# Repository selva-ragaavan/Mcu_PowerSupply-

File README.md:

# Mcu_PowerSupply-
This project implements a compact and reliable 5V regulated power supply designed to power microcontrollers and other 5V logic devices from a 12V DC source. Utilizing the LM2596 buck converter, it provides efficient voltage regulation, reverse polarity protection, and a USB Micro-B interface for seamless power delivery.
# Final Board:

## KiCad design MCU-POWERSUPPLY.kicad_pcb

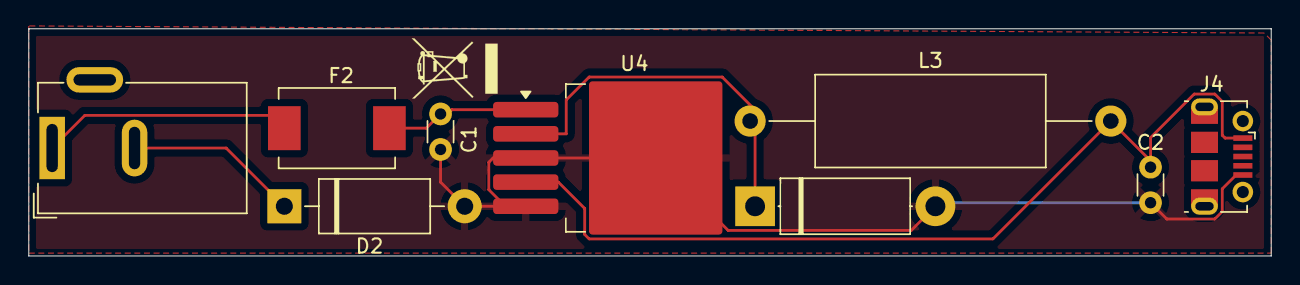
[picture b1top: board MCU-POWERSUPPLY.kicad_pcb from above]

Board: 2 copper layers, 87.5 x 16.0 mm, 9 parts (0 on the bottom side), 6 nets.

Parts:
C1: 680uf; C_Disc_D3.0mm_W1.6mm_P2.50mm
C2: 220uf; C_Disc_D3.0mm_W1.6mm_P2.50mm
D2: D_Schottky; D_DO-15_P12.70mm_Horizontal
F2: Fuse; Fuse_Bourns_MF-SM_7.98x5.44mm
IN5826: D1; D_5W_P12.70mm_Horizontal
J3: Barrel_Jack; BarrelJack_Wuerth_6941xx301002
J4: USB_B_Micro; USB_Micro-B_Molex-105017-0001
L3: 33uH; L_Axial_L16.0mm_D6.3mm_P25.40mm_Horizontal_Fastron_VHBCC
U4: LM2596S-5; TO-263-5_TabPin3

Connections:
+5V: C2.1, J4.1 (VBUS), L3.2, U4.4 (FB)
+12V: C1.1, F2.1, U4.1 (VIN)
GND: C1.2, C2.2, D2.2 (A), IN5826.2 (A), J4.5 (GND), U4.3 (GND), U4.5 (~ON/OFF)
unnamed: D2.1 (K), J3.2
unnamed: F2.2, J3.1
unnamed: IN5826.1 (K), L3.1, U4.2 (OUT)

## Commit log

2025-06-21 added project files
2025-06-21 Update README.md
    updated datasheet]
2025-06-23 Update README.md
    added usb datasheet
2025-06-23 updates done
2025-06-27 added final schematics
